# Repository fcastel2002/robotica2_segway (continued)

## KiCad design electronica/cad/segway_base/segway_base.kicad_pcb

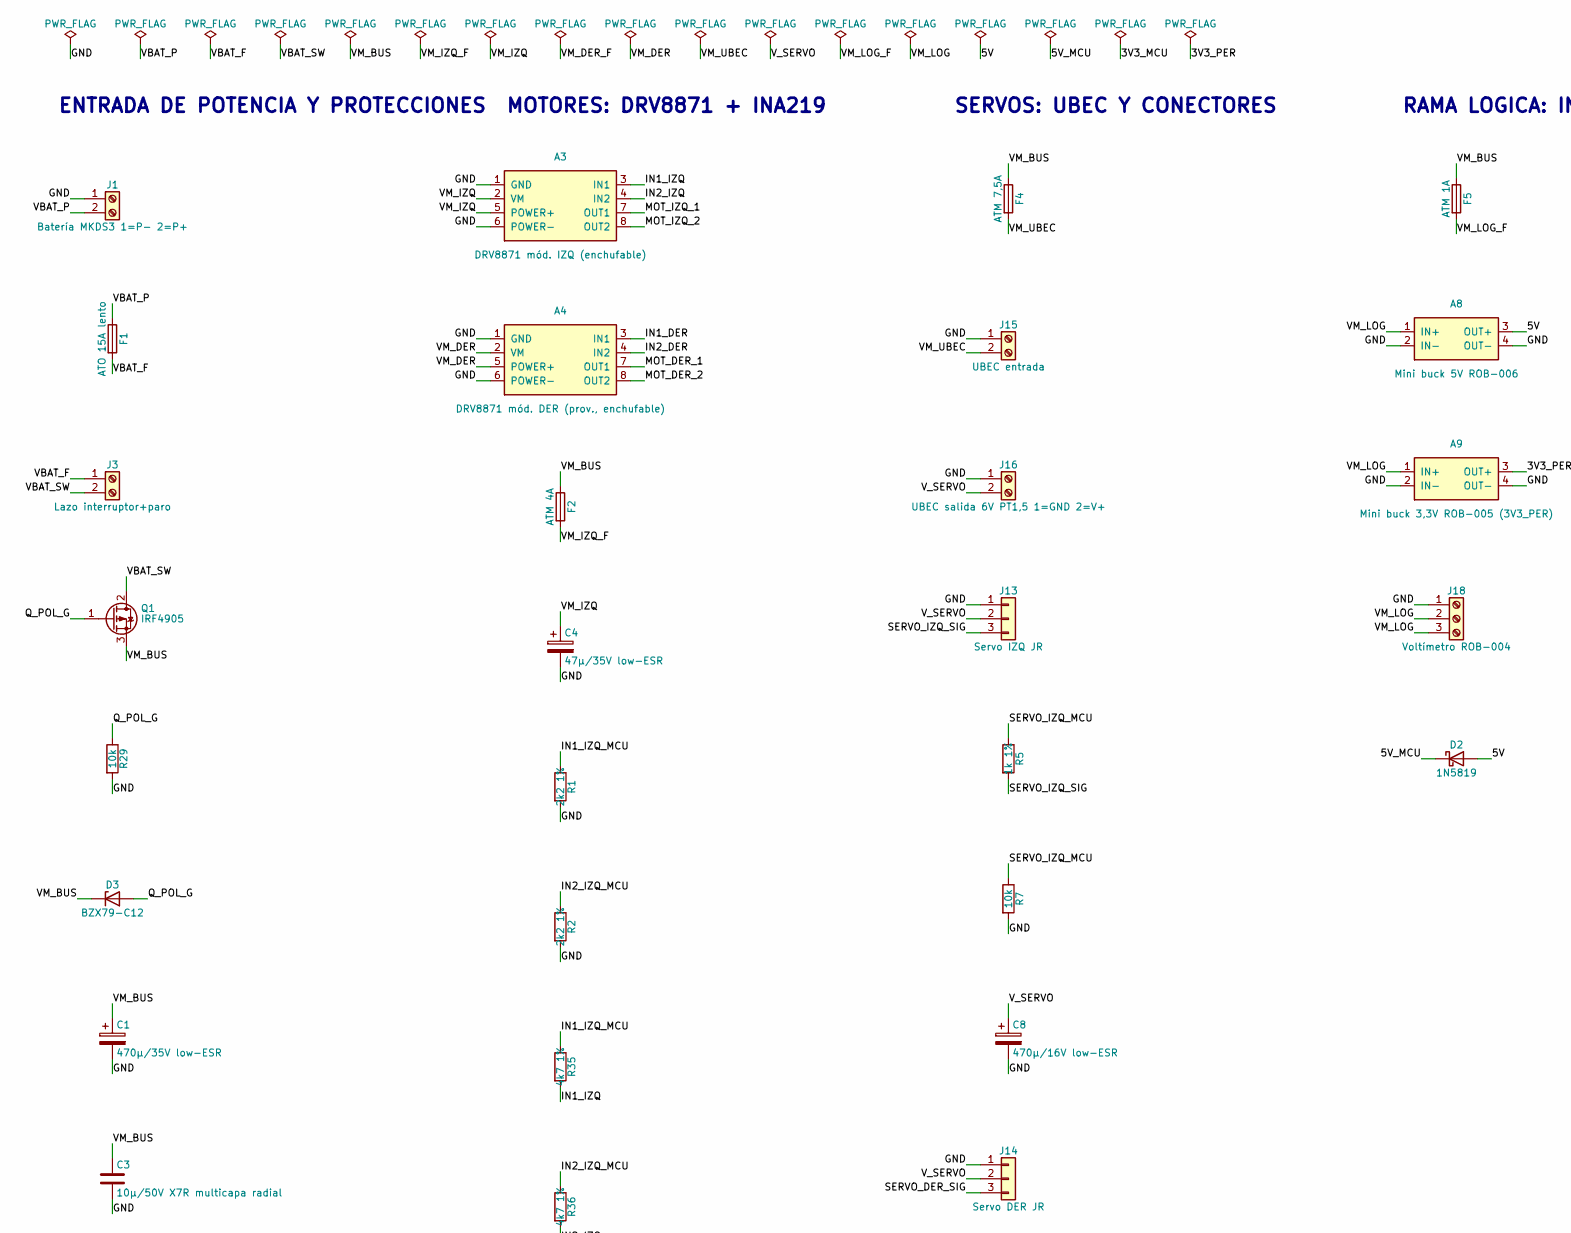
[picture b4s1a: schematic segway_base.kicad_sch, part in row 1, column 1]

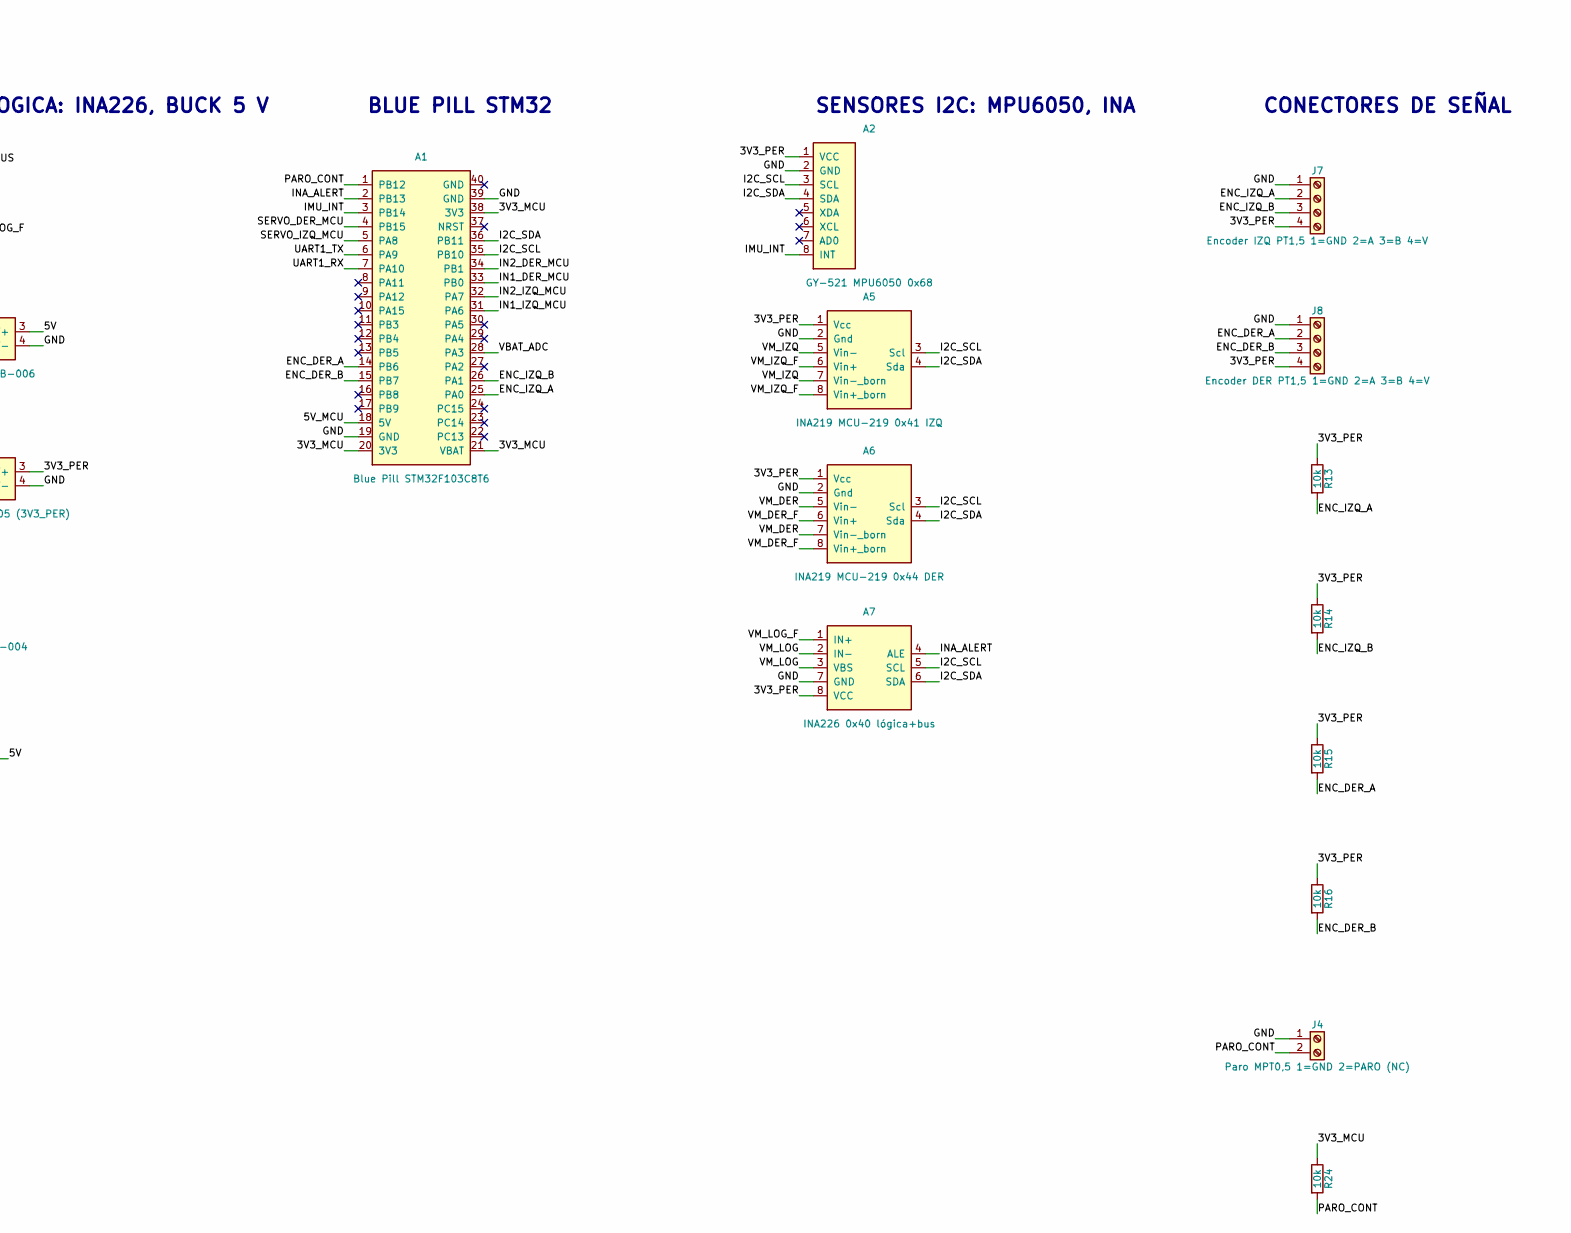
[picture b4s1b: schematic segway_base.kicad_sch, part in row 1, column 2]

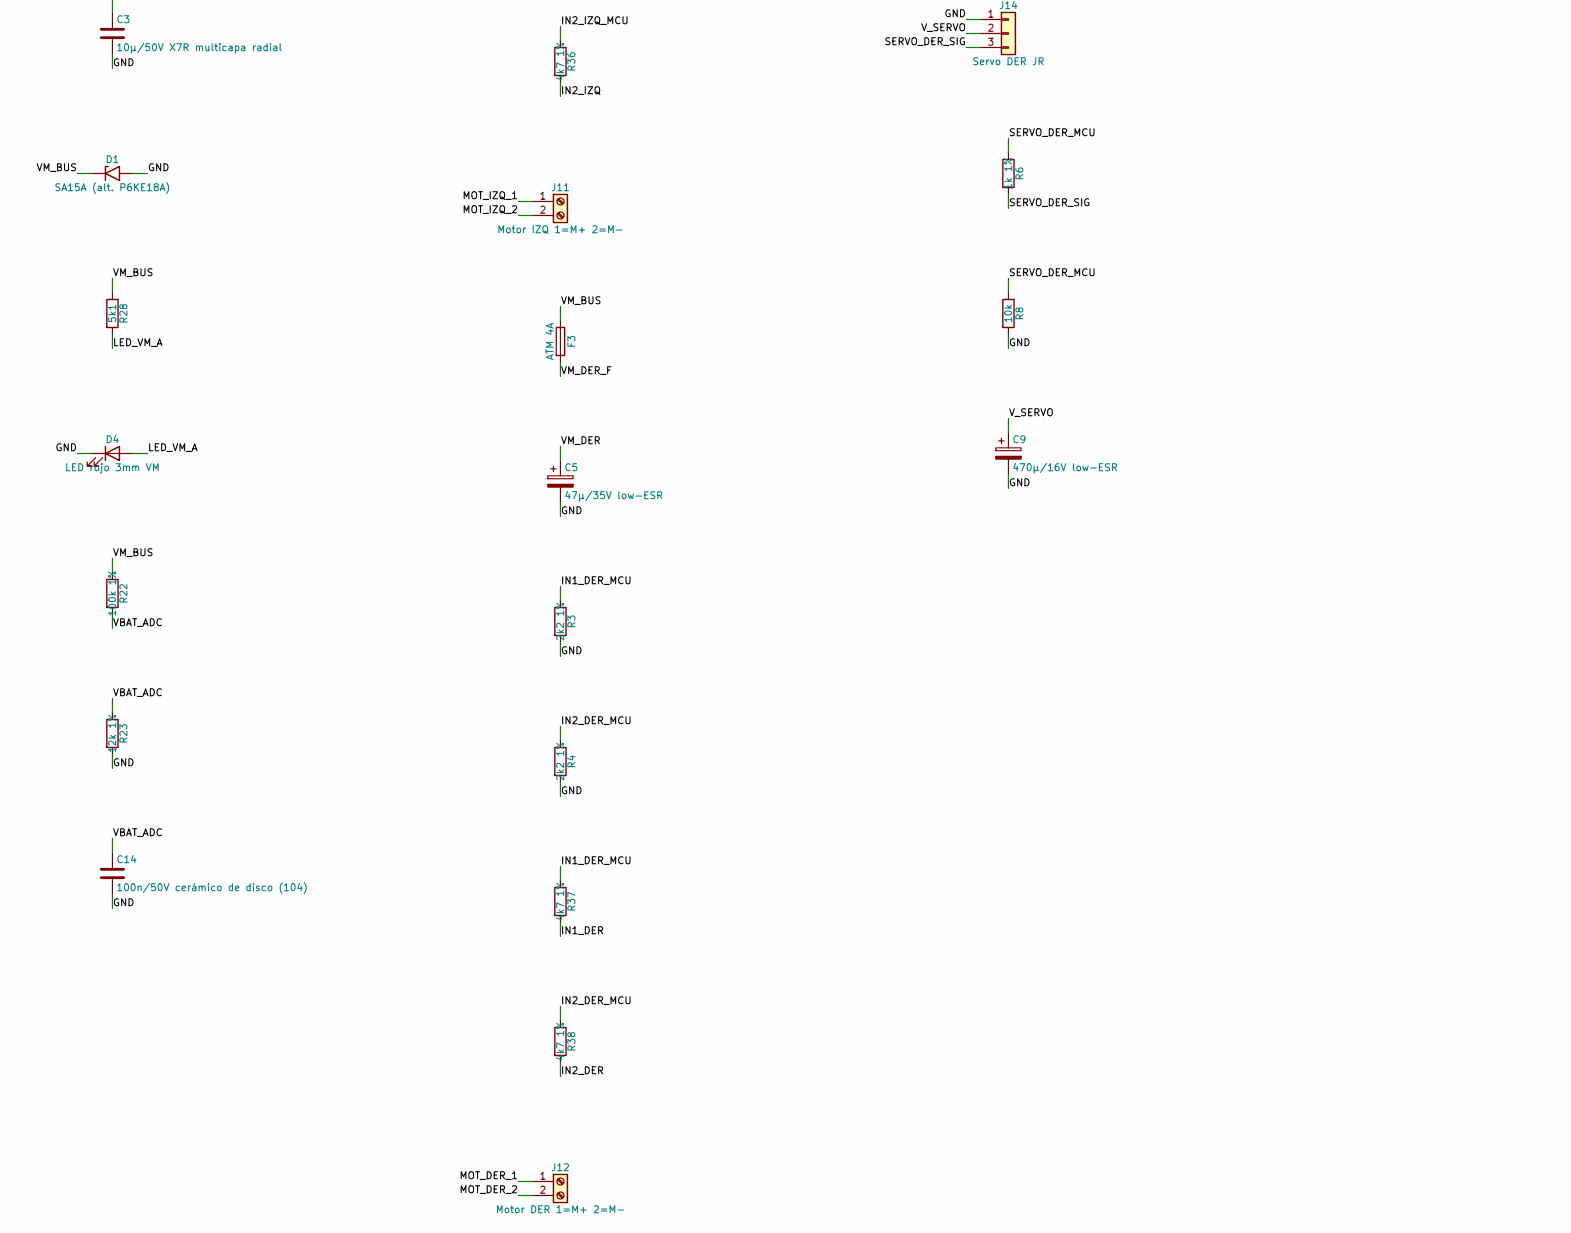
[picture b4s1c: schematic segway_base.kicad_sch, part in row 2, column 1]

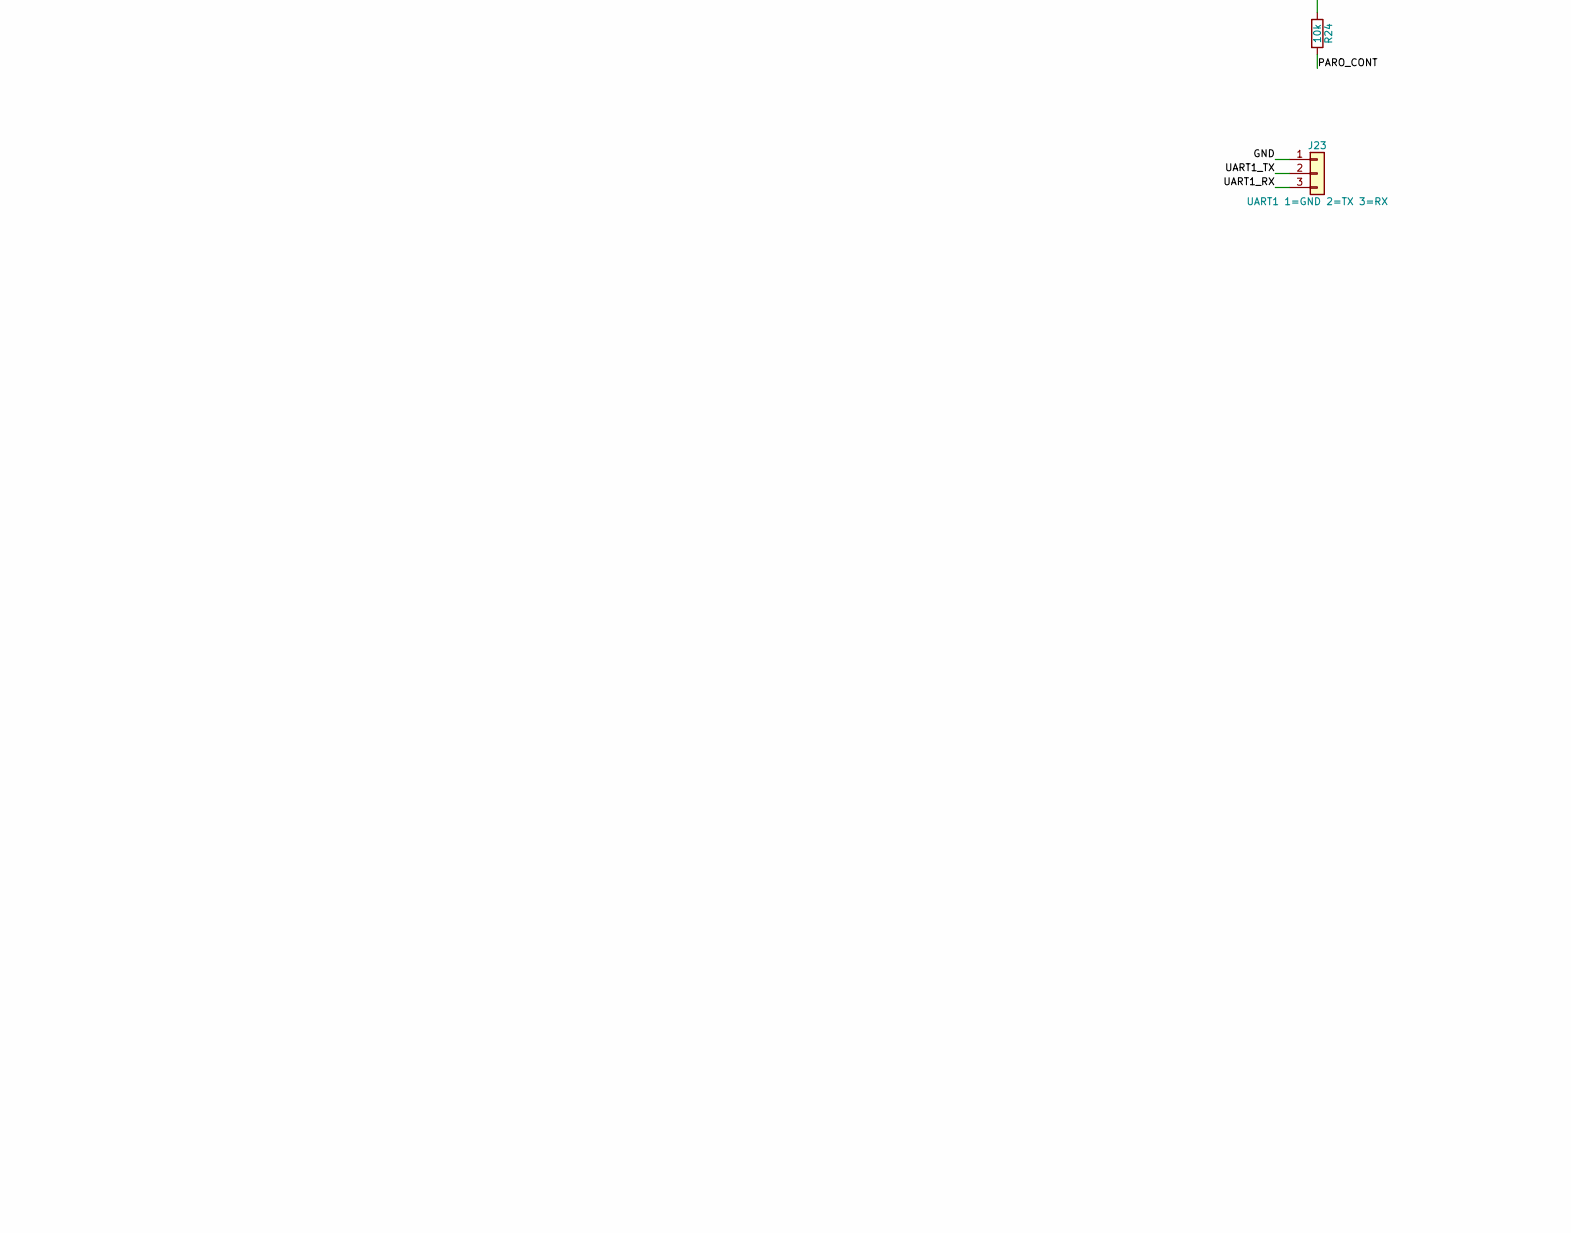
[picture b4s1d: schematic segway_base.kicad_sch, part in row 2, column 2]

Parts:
A1: Blue Pill STM32F103C8T6; ROB-012_BluePill_STM32F103C8_40p
A2: GY-521 MPU6050 0x68; ROB-013_MPU6050_modulo_8p
A3: DRV8871 mód. IZQ (enchufable); ROB-008_DRV8871_modulo_8p
A4: DRV8871 mód. DER (prov., enchufable); ROB-008_DRV8871_modulo_8p
A5: INA219 MCU-219 0x41 IZQ; ROB-002_INA219_MCU-219_8p
A6: INA219 MCU-219 0x44 DER; ROB-002_INA219_MCU-219_8p
A7: INA226 0x40 lógica+bus; ROB-009_INA226_modulo_8p
A8: Mini buck 5V ROB-006; ROB-005-006_MiniBuck_modulo_4p
A9: Mini buck 3,3V ROB-005 (3V3_PER); ROB-005-006_MiniBuck_modulo_4p
C1: 470µ/35V low-ESR; CP_Radial_D10.0mm_P5.00mm
C3: 10µ/50V X7R multicapa radial; C_Disc_D7.5mm_W5.0mm_P5.00mm
C4, C5: 47µ/35V low-ESR; CP_Radial_D6.3mm_P2.50mm
C8, C9: 470µ/16V low-ESR; CP_Radial_D8.0mm_P3.50mm
C14: 100n/50V cerámico de disco (104); C_Disc_D5.0mm_W2.5mm_P5.00mm
D1: SA15A (alt. P6KE18A); D_DO-15_P10.16mm_Horizontal
D2: 1N5819; D_DO-41_SOD81_P10.16mm_Horizontal
D3: BZX79-C12; D_DO-35_SOD27_P7.62mm_Horizontal
D4: LED rojo 3mm VM; LED_D3.0mm
F1: ATO 15A lento; Fuseholder_Blade_ATO_Littelfuse_Pudenz_2_Pin
F2, F3: ATM 4A; Fuseholder_Blade_Mini_Keystone_3568
F4: ATM 7,5A; Fuseholder_Blade_Mini_Keystone_3568
F5: ATM 1A; Fuseholder_Blade_Mini_Keystone_3568
J1: Batería MKDS3 1=P− 2=P+; TerminalBlock_Phoenix_MKDS-3-2-5.08_1x02_P5.08mm_Horizontal
J3: Lazo interruptor+paro; TerminalBlock_Phoenix_MKDS-3-2-5.08_1x02_P5.08mm_Horizontal
J4: Paro MPT0,5 1=GND 2=PARO (NC); TerminalBlock_Phoenix_MPT-0,5-2-2.54_1x02_P2.54mm_Horizontal
J7: Encoder IZQ PT1,5 1=GND 2=A 3=B 4=V; TerminalBlock_Phoenix_PT-1,5-4-3.5-H_1x04_P3.50mm_Horizontal
J8: Encoder DER PT1,5 1=GND 2=A 3=B 4=V; TerminalBlock_Phoenix_PT-1,5-4-3.5-H_1x04_P3.50mm_Horizontal
J11: Motor IZQ 1=M+ 2=M−; TerminalBlock_Phoenix_MKDS-1,5-2-5.08_1x02_P5.08mm_Horizont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
J12: Motor DER 1=M+ 2=M−; TerminalBlock_Phoenix_MKDS-1,5-2-5.08_1x02_P5.08mm_Horizont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
J13: Servo IZQ JR; PinHeader_1x03_P2.54mm_Vertical
J14: Servo DER JR; PinHeader_1x03_P2.54mm_Vertical
J15: UBEC entrada; TerminalBlock_Phoenix_MKDS-1,5-2-5.08_1x02_P5.08mm_Horizont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
J16: UBEC salida 6V PT1,5 1=GND 2=V+; TerminalBlock_Phoenix_PT-1,5-2-3.5-H_1x02_P3.50mm_Horizontal
J18: Voltímetro ROB-004; TerminalBlock_Phoenix_PT-1,5-3-3.5-H_1x03_P3.50mm_Horizontal
J23: UART1 1=GND 2=TX 3=RX; PinHeader_1x03_P2.54mm_Vertical
Q1: IRF4905; TO-220-3_Vertical
R1, R2, R3, R4: 2k2 1%; R_Axial_DIN0207_L6.3mm_D2.5mm_P10.16mm_Horizontal
R5, R6: 1k 1%; R_Axial_DIN0207_L6.3mm_D2.5mm_P10.16mm_Horizontal
R7, R8, R13, R14, R15, R16, R24, R29: 10k; R_Axial_DIN0207_L6.3mm_D2.5mm_P10.16mm_Horizontal
R22: 100k 1%; R_Axial_DIN0207_L6.3mm_D2.5mm_P10.16mm_Horizontal
R23: 12k 1%; R_Axial_DIN0207_L6.3mm_D2.5mm_P10.16mm_Horizontal
R28: 5k1; R_Axial_DIN0207_L6.3mm_D2.5mm_P10.16mm_Horizontal
R35, R36, R37, R38: 4k7 1%; R_Axial_DIN0207_L6.3mm_D2.5mm_P10.16mm_Horizontal

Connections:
/3V3_MCU: A1.20 (3V3), A1.21 (VBAT), A1.38 (3V3), R24.1
/3V3_PER: A2.1 (VCC), A5.1 (Vcc), A6.1 (Vcc), A7.8 (VCC), A9.3 (OUT+), J7.4, J8.4, R13.1, R14.1, R15.1, R16.1
/5V: A8.3 (OUT+), D2.2 (A)
/5V_MCU: A1.18 (5V), D2.1 (K)
/ENC_DER_A: A1.14 (PB6), J8.2, R15.2
/ENC_DER_B: A1.15 (PB7), J8.3, R16.2
/ENC_IZQ_A: A1.25 (PA0), J7.2, R13.2
/ENC_IZQ_B: A1.26 (PA1), J7.3, R14.2
/GND: A1.19 (GND), A1.39 (GND), A2.2 (GND), A3.1 (GND), A3.6 (POWER-), A4.1 (GND), A4.6 (POWER-), A5.2 (Gnd), A6.2 (Gnd), A7.7 (GND), A8.2 (IN-), A8.4 (OUT-), A9.2 (IN-), A9.4 (OUT-), C1.2, C3.2, C4.2, C5.2, C8.2, C9.2, C14.2, D1.2 (A2), D4.1 (K), J1.1, J4.1, J7.1, J8.1, J13.1, J14.1, J15.1, J16.1, J18.1, J23.1, R1.2, R2.2, R3.2, R4.2, R7.2, R8.2, R23.2, R29.2
/I2C_SCL: A1.35 (PB10), A2.3 (SCL), A5.3 (Scl), A6.3 (Scl), A7.5 (SCL)
/I2C_SDA: A1.36 (PB11), A2.4 (SDA), A5.4 (Sda), A6.4 (Sda), A7.6 (SDA)
/IMU_INT: A1.3 (PB14), A2.8 (INT)
/IN1_DER: A4.3 (IN1), R37.2
/IN1_DER_MCU: A1.33 (PB0), R3.1, R37.1
/IN1_IZQ: A3.3 (IN1), R35.2
/IN1_IZQ_MCU: A1.31 (PA6), R1.1, R35.1
/IN2_DER: A4.4 (IN2), R38.2
/IN2_DER_MCU: A1.34 (PB1), R4.1, R38.1
/IN2_IZQ: A3.4 (IN2), R36.2
/IN2_IZQ_MCU: A1.32 (PA7), R2.1, R36.1
/INA_ALERT: A1.2 (PB13), A7.4 (ALE)
/LED_VM_A: D4.2 (A), R28.2
/MOT_DER_1: A4.7 (OUT1), J12.1
/MOT_DER_2: A4.8 (OUT2), J12.2
/MOT_IZQ_1: A3.7 (OUT1), J11.1
/MOT_IZQ_2: A3.8 (OUT2), J11.2
/PARO_CONT: A1.1 (PB12), J4.2, R24.2
/Q_POL_G: D3.2 (A), Q1.1 (G), R29.1
/SERVO_DER_MCU: A1.4 (PB15), R6.1, R8.1
/SERVO_DER_SIG: J14.3, R6.2
/SERVO_IZQ_MCU: A1.5 (PA8), R5.1, R7.1
/SERVO_IZQ_SIG: J13.3, R5.2
/UART1_RX: A1.7 (PA10), J23.3
/UART1_TX: A1.6 (PA9), J23.2
/VBAT_ADC: A1.28 (PA3), C14.1, R22.2, R23.1
/VBAT_F: F1.2, J3.1
/VBAT_P: F1.1, J1.2
/VBAT_SW: J3.2, Q1.2 (D)
/VM_BUS: C1.1, C3.1, D1.1 (A1), D3.1 (K), F2.1, F3.1, F4.1, F5.1, Q1.3 (S), R22.1, R28.1
/VM_DER: A4.2 (VM), A4.5 (POWER+), A6.5 (Vin-), A6.7 (Vin-_born), C5.1
/VM_DER_F: A6.6 (Vin+), A6.8 (Vin+_born), F3.2
/VM_IZQ: A3.2 (VM), A3.5 (POWER+), A5.5 (Vin-), A5.7 (Vin-_born), C4.1
/VM_IZQ_F: A5.6 (Vin+), A5.8 (Vin+_born), F2.2
/VM_LOG: A7.2 (IN-), A7.3 (VBS), A8.1 (IN+), A9.1 (IN+), J18.2, J18.3
/VM_LOG_F: A7.1 (IN+), F5.2
/VM_UBEC: F4.2, J15.2
/V_SERVO: C8.1, C9.1, J13.2, J14.2, J16.2

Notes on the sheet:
BLUE PILL STM32
SENSORES I2C: MPU6050, INA
MOTORES: DRV8871 + INA219
ENTRADA DE POTENCIA Y PROTECCIONES
SERVOS: UBEC Y CONECTORES
RAMA LOGICA: INA226, BUCK 5 V
CONECTORES DE SEÑAL

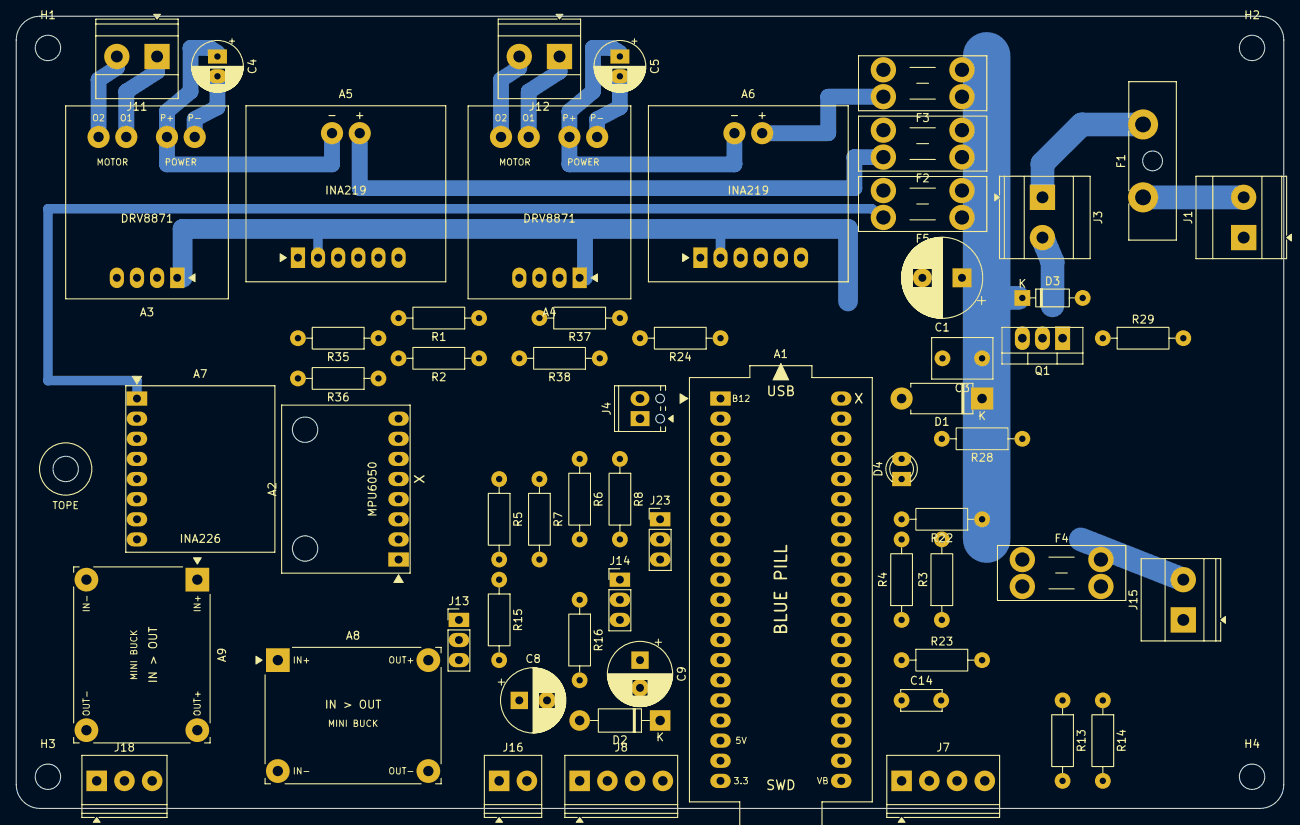
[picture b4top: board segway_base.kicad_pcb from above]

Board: 2 copper layers, 160.0 x 100.0 mm, 64 parts (0 on the bottom side), 47 nets.

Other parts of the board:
H1, H2, H3, H4: M3; MountingHole_3.2mm_M3

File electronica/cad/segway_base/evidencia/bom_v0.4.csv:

"Ref","Valor","Huella","Cantidad"
"A1","Blue Pill STM32F103C8T6","segway_modulos:ROB-012_BluePill_STM32F103C8_40p","1"
"A2","GY-521 MPU6050 0x68","segway_modulos:ROB-013_MPU6050_modulo_8p","1"
"A3","DRV8871 mód. IZQ (enchufable)","segway_modulos:ROB-008_DRV8871_modulo_8p","1"
"A4","DRV8871 mód. DER (prov., enchufable)","segway_modulos:ROB-008_DRV8871_modulo_8p","1"
"A5","INA219 MCU-219 0x41 IZQ","segway_modulos:ROB-002_INA219_MCU-219_8p","1"
"A6","INA219 MCU-219 0x44 DER","segway_modulos:ROB-002_INA219_MCU-219_8p","1"
"A7","INA226 0x40 lógica+bus","segway_modulos:ROB-009_INA226_modulo_8p","1"
"A8","Mini buck 5V ROB-006","segway_modulos:ROB-005-006_MiniBuck_modulo_4p","1"
"A9","Mini buck 3,3V ROB-005 (3V3_PER)","segway_modulos:ROB-005-006_MiniBuck_modulo_4p","1"
"C1","470µ/35V low-ESR","Capacitor_THT:CP_Radial_D10.0mm_P5.00mm","1"
"C3","10µ/50V X7R multicapa radial","Capacitor_THT:C_Disc_D7.5mm_W5.0mm_P5.00mm","1"
"C4,C5","47µ/35V low-ESR","Capacitor_THT:CP_Radial_D6.3mm_P2.50mm","2"
"C8,C9","470µ/16V low-ESR","Capacitor_THT:CP_Radial_D8.0mm_P3.50mm","2"
"C14","100n/50V cerámico de disco (104)","Capacitor_THT:C_Disc_D5.0mm_W2.5mm_P5.00mm","1"
"D1","SA15A (alt. P6KE18A)","Diode_THT:D_DO-15_P10.16mm_Horizontal","1"
"D2","1N5819","Diode_THT:D_DO-41_SOD81_P10.16mm_Horizontal","1"
"D3","BZX79-C12","Diode_THT:D_DO-35_SOD27_P7.62mm_Horizontal","1"
"D4","LED rojo 3mm VM","LED_THT:LED_D3.0mm","1"
"F1","ATO 15A lento","Fuse:Fuseholder_Blade_ATO_Littelfuse_Pudenz_2_Pin","1"
"F2,F3","ATM 4A","Fuse:Fuseholder_Blade_Mini_Keystone_3568","2"
"F4","ATM 7,5A","Fuse:Fuseholder_Blade_Mini_Keystone_3568","1"
"F5","ATM 1A","Fuse:Fuseholder_Blade_Mini_Keystone_3568","1"
"J1","Batería MKDS3 1=P− 2=P+","TerminalBlock_Phoenix:TerminalBlock_Phoenix_MKDS-3-2-5.08_1x02_P5.08mm_Horizontal","1"
"J3","Lazo interruptor+paro","TerminalBlock_Phoenix:TerminalBlock_Phoenix_MKDS-3-2-5.08_1x02_P5.08mm_Horizontal","1"
"J4","Paro MPT0,5 1=GND 2=PARO (NC)","TerminalBlock_Phoenix:TerminalBlock_Phoenix_MPT-0,5-2-2.54_1x02_P2.54mm_Horizontal","1"
"J7","Encoder IZQ PT1,5 1=GND 2=A 3=B 4=V","TerminalBlock_Phoenix:TerminalBlock_Phoenix_PT-1,5-4-3.5-H_1x04_P3.50mm_Horizontal","1"
"J8","Encoder DER PT1,5 1=GND 2=A 3=B 4=V","TerminalBlock_Phoenix:TerminalBlock_Phoenix_PT-1,5-4-3.5-H_1x04_P3.50mm_Horizontal","1"
"J11","Motor IZQ 1=M− 2=M+","TerminalBlock_Phoenix:TerminalBlock_Phoenix_MKDS-1,5-2-5.08_1x02_P5.08mm_Horizontal","1"
"J12","Motor DER 1=M− 2=M+","TerminalBlock_Phoenix:TerminalBlock_Phoenix_MKDS-1,5-2-5.08_1x02_P5.08mm_Horizontal","1"
"J13","Servo IZQ JR","Connector_PinHeader_2.54mm:PinHeader_1x03_P2.54mm_Vertical","1"
"J14","Servo DER JR","Connector_PinHeader_2.54mm:PinHeader_1x03_P2.54mm_Vertical","1"
"J15","UBEC entrada","TerminalBlock_Phoenix:TerminalBlock_Phoenix_MKDS-1,5-2-5.08_1x02_P5.08mm_Horizontal","1"
"J16","UBEC salida 6V PT1,5 1=GND 2=V+","TerminalBlock_Phoenix:TerminalBlock_Phoenix_PT-1,5-2-3.5-H_1x02_P3.50mm_Horizontal","1"
"J18","Voltímetro ROB-004","TerminalBlock_Phoenix:TerminalBlock_Phoenix_PT-1,5-3-3.5-H_1x03_P3.50mm_Horizontal","1"
"J23","UART1 1=GND 2=TX 3=RX","Connector_PinHeader_2.54mm:PinHeader_1x03_P2.54mm_Vertical","1"
"Q1","IRF4905","Package_TO_SOT_THT:TO-220-3_Vertical","1"
"R1,R2,R3,R4","2k2 1%","Resistor_THT:R_Axial_DIN0207_L6.3mm_D2.5mm_P10.16mm_Horizontal","4"
"R5,R6","1k 1%","Resistor_THT:R_Axial_DIN0207_L6.3mm_D2.5mm_P10.16mm_Horizontal","2"
"R7,R8,R13,R14,R15,R16,R24,R29","10k","Resistor_THT:R_Axial_DIN0207_L6.3mm_D2.5mm_P10.16mm_Horizontal","8"
"R22","100k 1%","Resistor_THT:R_Axial_DIN0207_L6.3mm_D2.5mm_P10.16mm_Horizontal","1"
"R23","12k 1%","Resistor_THT:R_Axial_DIN0207_L6.3mm_D2.5mm_P10.16mm_Horizontal","1"
"R28","5k1","Resistor_THT:R_Axial_DIN0207_L6.3mm_D2.5mm_P10.16mm_Horizontal","1"
"R35,R36,R37,R38","4k7 1%","Resistor_THT:R_Axial_DIN0207_L6.3mm_D2.5mm_P10.16mm_Horizontal","4"

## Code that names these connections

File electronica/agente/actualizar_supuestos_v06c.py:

"""Supuestos de la expansión de la placa de lógica (ELE-037, 26/10/2026): tiras J24/J25/J26 y pin 11 del cable."""
import json
import re
from pathlib import Path

BASE = Path(__file__).resolve().parents[2] / "electronica" / "cad" / "segway_base"
FECHA = "26/10/2026"
FUENTE = "Pedido del equipo del 26/10/2026 [M]: pines hembra en paralelo a la controladora (ELE-037)"

CAMBIOS = {
    "SUP-72": dict(estado="CAMBIADO", tema="Cable entre placas (J20)",
                   supuesto="IDC macho de 2 × 8 pines a 2,54 mm en cada placa y cable plano de 16 hilos recto (pin n con pin n). 1 VBAT_ADC, 2 SERVO_IZQ, 3 INA_ALERT, 4 SERVO_DER, 5 SDA, 6 IN2_DER, 7 SCL, 8 IN1_DER, 9 3V3, 10 IN2_IZQ, 11 sin conexión en las dos placas, 12 IN1_IZQ, 13 y 14 5V_MCU, 15 y 16 GND.",
                   base="cad/interconexion_v0.6.json; ruteo v0.1 de las dos placas [H]. El pin 11 quedó encerrado en la potencia por el bus I2C y en la lógica por el 5V de J26.",
                   impacto="Otro orden obliga a rehacer el ruteo de las dos placas.",
                   confirma="Mecánica fija el largo; continuidad pin a pin del cable armado.",
                   valor={"pines": 16, "paso_mm": 2.54, "sin_conexion": [11]}),
    "SUP-77": dict(estado="ASUMIDO", tema="Masa de la lógica en la placa de potencia",
                   supuesto="El relleno GND de la banda lógica se une al bus de retorno de los servos (que va al lomo por J15) y al lomo por D4. Los retornos de los motores tienen ramas propias por el borde superior. El retorno de la lógica usa J20.15 y J20.16; J20.11 queda sin conexión en las dos placas.",
                   base="Criterio de masa en estrella (§10 de diseno_v0.3.md) adaptado al ruteo de una cara [H].",
                   impacto="La corriente de los servos comparte unos 20 mm de cobre con la masa de la lógica.",
                   confirma="E-03: medir la diferencia de GND entre J20.15 y C1− con los servos en carga.",
                   valor={}),
}

NUEVOS = [
    dict(id="SUP-78", grupo="I", tema="Tiras de expansión junto a la ESP32-S3 (J24, J25)",
         supuesto="Dos tiras hembra de 1 × 22 a 2,54 mm pegadas por fuera a las hileras de A1, pin a pin: J24.n = A1.n y J25.n = A1.(22 + n). Los pines sin uso de A1 tienen net propia con su nombre (GPIO1, RST…). Libres para sensores: GPIO1, 2, 21, 38-42 y 47. La DevKitC mide 28 mm de ancho con hileras a 25,4 mm: su borde queda a 1,3 mm de cada hilera y el Dupont enchufado en la tira, a 1,27 mm. Los courtyards de J24/J25 se recortaron de ese lado para no chocar con el de A1.",
         base="Pedido del equipo del 26/10/2026 [M]; ancho de 28 mm del vendedor (dimensiones_vendedor.jpg) [V]; separación de 25,40 mm (SUP-22) [H].",
         impacto="Si la DevKitC es más ancha, los Dupont de J24/J25 no entran con la ESP32 enchufada: hay que usar cables con el plástico recortado o soldar a los pads.",
         confirma="E-01: medir el ancho de la DevKitC y probar en seco un Dupont en la tira con la ESP32 enchufada.",
         valor={"libres": ["GPIO1", "GPIO2", "GPIO21", "GPIO38", "GPIO39", "GPIO40", "GPIO41", "GPIO42", "GPIO47"]}),
    dict(id="SUP-79", grupo="I", tema="Alimentación de la expansión (J26)",
         supuesto="J26, tira hembra de 1 × 6: 1-2 GND, 3-4 3V3_MCU y 5-6 5V_MCU. Presupuesto para todos los sensores: unos 300 mA en 5V y 150 mA en 3V3. El 5V viene del buck A8 por D2 (1N5819, 1 A) y los pines 13-14 del cable, y llega con unos 4,6-4,7 V. El 3V3 sale del regulador de la DevKitC (SUP-25), que ya alimenta la ESP32-S3, la MPU, los INA y los encoders.",
         base="D2 de 1 A (SUP-17), F5 de 1 A en VM_LOG (SUP-49), regulador SOT-223 de clase 1 A (SUP-25) y consumo de unos 350 mA de pico de la ESP32-S3 (SUP-31) [H].",
         impacto="Con más consumo en 3V3, el regulador de la DevKitC calienta y puede reiniciar la ESP32. Con más consumo en 5V, D2 y F5 quedan al límite.",
         confirma="E-02: medir 5V_MCU y 3V3 en J26 con los sensores conectados y Wi-Fi activo, y la temperatura del regulador de la DevKitC.",
         valor={"5V_mA": 300, "3V3_mA": 150}),
]


def fila(i, n):
    return f"| {i} | {n['tema']} | {n['supuesto']} | {n['base']} | {n['impacto']} | {n['confirma']} | {n['estado']} | {FECHA} |"


def main():
    js = BASE / "supuestos.json"
    d = json.loads(js.read_text(encoding="utf-8"))
    for it in d["items"]:
        n = CAMBIOS.get(it["id"])
        if n:
            it["historial"].append({"fecha": FECHA, "antes": {k: it[k] for k in ("tema", "supuesto", "estado")}, "fuente": FUENTE})
            it.update(tema=n["tema"], supuesto=n["supuesto"], base=n["base"], impacto_si_cambia=n["impacto"],
                      como_se_confirma=n["confirma"], estado=n["estado"], fecha=FECHA, valor=n["valor"])
    ids = {it["id"] for it in d["items"]}
    for n in NUEVOS:
        if n["id"] not in ids:
            d["items"].append({"grupo": n["grupo"], "tema": n["tema"], "supuesto": n["supuesto"], "base": n["base"],
                               "impacto_si_cambia": n["impacto"], "como_se_confirma": n["confirma"], "estado": "ASUMIDO",
                               "fecha": FECHA, "refs": [], "afecta": ["pcb", "firmware"], "alias": [], "id": n["id"],
                               "valor": n["valor"], "historial": []})
    d["fecha"] = FECHA
    d["revision_lista"] = d.get("revision_lista", 1) + 1
    js.write_text(json.dumps(d, ensure_ascii=False, indent=1), encoding="utf-8")

    md = BASE / "supuestos.md"
    t = md.read_text(encoding="utf-8")
    for i, n in CAMBIOS.items():
        t, k = re.subn(rf"^\| {i} \|.*$", fila(i, n), t, count=1, flags=re.M)
        assert k == 1, i
    if "| SUP-78 |" not in t:
        filas = "\n".join(fila(n["id"], dict(n, estado="ASUMIDO")) for n in NUEVOS)
        k = t.index("\n\n## Dónde medir sin puntos de prueba")
        t = t[:k] + "\n" + filas + t[k:]
        t = t.rstrip() + (f"\n| {FECHA} | SUP-72, SUP-77; nuevos SUP-78 y SUP-79 | Expansión de la placa de lógica: tiras J24/J25 "
                          f"junto a la ESP32-S3 y J26 de alimentación; J20.11 sin conexión en las dos placas | {FUENTE} |\n")
    md.write_text(t, encoding="utf-8")
    print("actualizados:", ", ".join(CAMBIOS), "| nuevos:", ", ".join(n["id"] for n in NUEVOS))


if __name__ == "__main__":
    main()

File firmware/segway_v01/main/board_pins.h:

// Asignación de pines del prototipo v0.1 (ESP32-S3 N16R8, clon DevKitC-1).
// Valores por defecto: cambiarlos acá cuando se defina el cableado real.
//
// No usar:
//   19, 20     USB nativo (sin uso: consola y flasheo van por UART0)
//   26-37      flash y PSRAM octal del módulo N16R8
//   45, 46     pines de arranque (el 0 solo como entrada de botón; el 3 también es de arranque,
//              pero solo para JTAG si se graba el eFuse STRAP_JTAG_SEL: no grabarlo)
//   43, 44     UART0: consola y comandos (conector UART de la placa)
#pragma once

// Bus I2C compartido: MPU-6050 ahora, INA226 más adelante
#define PIN_I2C_SDA         17
#define PIN_I2C_SCL         16
#define PIN_IMU_INT         18      // reservado: temporizar el lazo con la IMU
#define PIN_INA_ALERT       8       // INA226


// L298N: PWM en IN1/IN2 (IN3/IN4 para el derecho) y habilitación en ENA/ENB.
// Quitar los puentes ENA/ENB del módulo para conectarlos al ESP32. Si se dejan puestos,
// poner el EN en -1: funciona igual, pero al desarmar las ruedas quedan frenadas, no libres.
// Para el DRV8871 (sin EN) también va -1.
#define PIN_MOTOR_L_IN1     14
#define PIN_MOTOR_L_IN2     13
#define PIN_MOTOR_L_EN      1
#define PIN_MOTOR_R_IN1     12
#define PIN_MOTOR_R_IN2     11
#define PIN_MOTOR_R_EN      -1
// Reservado: entrada de falla del MCPWM (parada de emergencia o comparador de sobrecorriente).
// Cortaría los dos motores por hardware, sin pasar por la CPU. Aún no se configura.
#define PIN_MOTOR_FAULT     21

// Servos de las patas (señal; la alimentación va por el UBEC, con GND común)
#define PIN_SERVO_L         9       // sobre el motor izquierdo (J13 de la PCB)
#define PIN_SERVO_R         10      // sobre el motor derecho (J14 de la PCB)

// Encoders de cuadratura de las ruedas (hall del motor, alimentados a 3,3 V: las salidas
// no pueden subir a 5 V, los GPIO del ESP32 no lo toleran)
// 29/10: medido con los motores (el motor izquierdo movía las cuentas de 13/14 y el derecho las
// de 11/12): el encoder izquierdo está cableado en 13/14 y el derecho en 11/12
#define PIN_ENC_L_A         4
#define PIN_ENC_L_B         5
#define PIN_ENC_R_A         7
#define PIN_ENC_R_B         15

// Sensor de distancia al piso para el escalón (Sharp GP2Y0A60SZLF en J27, SUP-82): su salida
// entra por un divisor 10k/15k (x 0,6). ADC1_CH2, convive con el WiFi.
#define PIN_DIST_SUELO      3

// LED RGB integrado (WS2812), indica el estado del robot
#define PIN_LED_RGB         48      // 38 en la versión 1.1 de la DevKitC

// Reservados para versiones posteriores (no se configuran en la v0.1)
#define PIN_BATT_ADC        1       // debe ser ADC1 (GPIO1-10) para convivir con WiFi
#define PIN_ARM_BUTTON      0       // botón BOOT de la placa

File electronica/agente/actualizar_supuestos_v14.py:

"""Supuestos de la PCB v0.4 (31/10/2026): textos que quedaron viejos (VBAT_ADC, D4.1, mechas, codificación de los bucks)."""
import collections
import json
import re
from pathlib import Path

BASE = Path(__file__).resolve().parents[2] / "electronica" / "cad" / "segway_base"
FECHA = "31/10/2026"
FOTOS = "Fotos de los módulos comprados (componentes_comprados/fotos/), medidas con el paso de 2,54 mm de las tiras como escala [M]"
FUENTE = "Repaso de la lista al cerrar la v0.4: textos desactualizados respecto de las placas"
CLAVE = {"supuesto": "supuesto", "base": "base", "impacto": "impacto_si_cambia", "confirma": "como_se_confirma", "estado": "estado"}

CAMPOS = {
    "SUP-11": {"supuesto": "Mechas que pide la v0.4 (informes de taladros de cada placa): 0,8; 0,9; 1,0; 1,1; 1,2; 1,3; 1,5; 1,8; 2,0; 2,5 y 3,2 mm (minitaladro). Resistencias y diodos chicos: 0,8-0,9 mm. Tiras de 2,54 mm y TO-220: 1,0 mm. Borneras, portafusibles, electrolíticos y diodos DO-15: 1,1-1,8 mm. Pads de los mini buck: 1,5 mm (absorben el error de medida). Anillo mínimo de 0,5 mm (0,6 mm en potencia). Cada pad deja un punto central sin cobre de 0,5 mm como guía para la mecha. Si falta alguna mecha, se usa la inmediata superior.",
               "confirma": "Matías informa qué mechas tiene. Probar cada mecha con una bornera y con un pin de la tira antes de taladrar la placa."},
    "SUP-24": {"supuesto": "Sin conexión: GPIO35, 36 y 37 (PSRAM octal del N16R8), GPIO0, 45 y 46 (strapping), GPIO19 y 20 (USB nativo), GPIO43 y 44 (UART0 del CH343P), GPIO48 (LED RGB WS2812) y RST. GPIO3 queda libre desde la v0.4 (solo en J24.13): su función de strapping (fuente de JTAG) solo actúa con el eFuse STRAP_JTAG_SEL grabado, que de fábrica no lo está.",
               "confirma": "Primer arranque de la ESP32 montada."},
    "SUP-38": {"supuesto": "A8 y A9 son los únicos bucks de cada placa, así que no se confunden con otro módulo igual. Van soldados (no hay tope mecánico posible: los 4 pads forman un rectángulo). Lo que protege es el procedimiento: rótulo «IN» en el cobre, pad cuadrado en IN+ y la prueba de continuidad IN+/OUT+ antes de alimentar (SUP-37). A7 (INA226) quedó sin agujero de tope (SUP-75) y va soldado."},
    "SUP-72": {"supuesto": "IDC macho de 2 × 8 pines a 2,54 mm en cada placa y cable plano de 16 hilos recto (pin n con pin n). 1 sin conexión, 2 SERVO_IZQ, 3 INA_ALERT, 4 SERVO_DER, 5 SDA, 6 IN2_DER, 7 SCL, 8 IN1_DER, 9 3V3, 10 IN2_IZQ, 11 sin conexión, 12 IN1_IZQ, 13 y 14 5V_MCU, 15 y 16 GND."},
    "SUP-77": {"supuesto": "En la potencia v0.4 el relleno GND de la banda lógica toca el bus de retorno de los servos (y 80,5), que baja en x 76,5 a un bus inferior hasta J15 y el lomo; además se une al lomo por una rama en y 57,66 (la que antes iba a D4.1). El lazo principal de los servos cierra por J16.1, pero parte del retorno puede pasar por el relleno. J20.1 y J20.11 quedan sin conexión en las dos placas."},
}


def fila(it):
    return (f"| {it['id']} | {it['tema']} | {it['supuesto']} | {it['base']} | {it['impacto_si_cambia']} | "
            f"{it['como_se_confirma']} | {it['estado']} | {it['fecha']} |")


def main():
    js = BASE / "supuestos.json"
    d = json.loads(js.read_text(encoding="utf-8"))
    por_id = {it["id"]: it for it in d["items"]}
    for i, campos in CAMPOS.items():
        it = por_id[i]
        it["historial"].append({"fecha": FECHA, "antes": {CLAVE[k]: it[CLAVE[k]] for k in campos}, "fuente": FUENTE})
        for k, v in campos.items():
            it[CLAVE[k]] = v
        it["fecha"] = FECHA
    d["fecha"] = FECHA
    d["revision_lista"] = d.get("revision_lista", 1) + 1
    js.write_text(json.dumps(d, ensure_ascii=False, indent=1), encoding="utf-8")
    md = BASE / "supuestos.md"
    t = md.read_text(encoding="utf-8")
    for i in CAMPOS:
        t, k = re.subn(rf"^\| {i} \|.*$", lambda m: fila(por_id[i]), t, count=1, flags=re.M)
        assert k == 1, i
    t = t.rstrip() + (f"\n| {FECHA} | {', '.join(CAMPOS)} | Textos al día con la v0.4: GPIO3 libre, pin 1 del cable sin conexión, "
                      f"mechas de los informes de taladros, bucks sin tope y rama de masa de la ex-D4.1 | {FUENTE} |\n")
    c = collections.Counter(it["estado"] for it in d["items"])
    t = re.sub(r"Estado: \*\*\d+ supuestos\*\*: \d+ asumidos, \d+ cambiados y \d+ confirmados?\.",
               f"Estado: **{len(d['items'])} supuestos**: {c['ASUMIDO']} asumidos, {c['CAMBIADO']} cambiados y {c['CONFIRMADO']} confirmados.", t, count=1)
    md.write_text(t, encoding="utf-8")
    print(dict(c))


if __name__ == "__main__":
    main()
